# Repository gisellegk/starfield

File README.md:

# Starfield
May the force be with you

Arduino Libraries:
- [kriswiner/LP5036](https://github.com/kriswiner/LP5036/tree/master)
- [JackDaviesDesign/Pimoroni-11x7-LED-Matrix-Arduino](https://github.com/JackDaviesDesign/Pimoroni-11x7-LED-Matrix-Arduino)

Font:
- [Star Jedi](https://www.dafont.com/star-jedi.font)

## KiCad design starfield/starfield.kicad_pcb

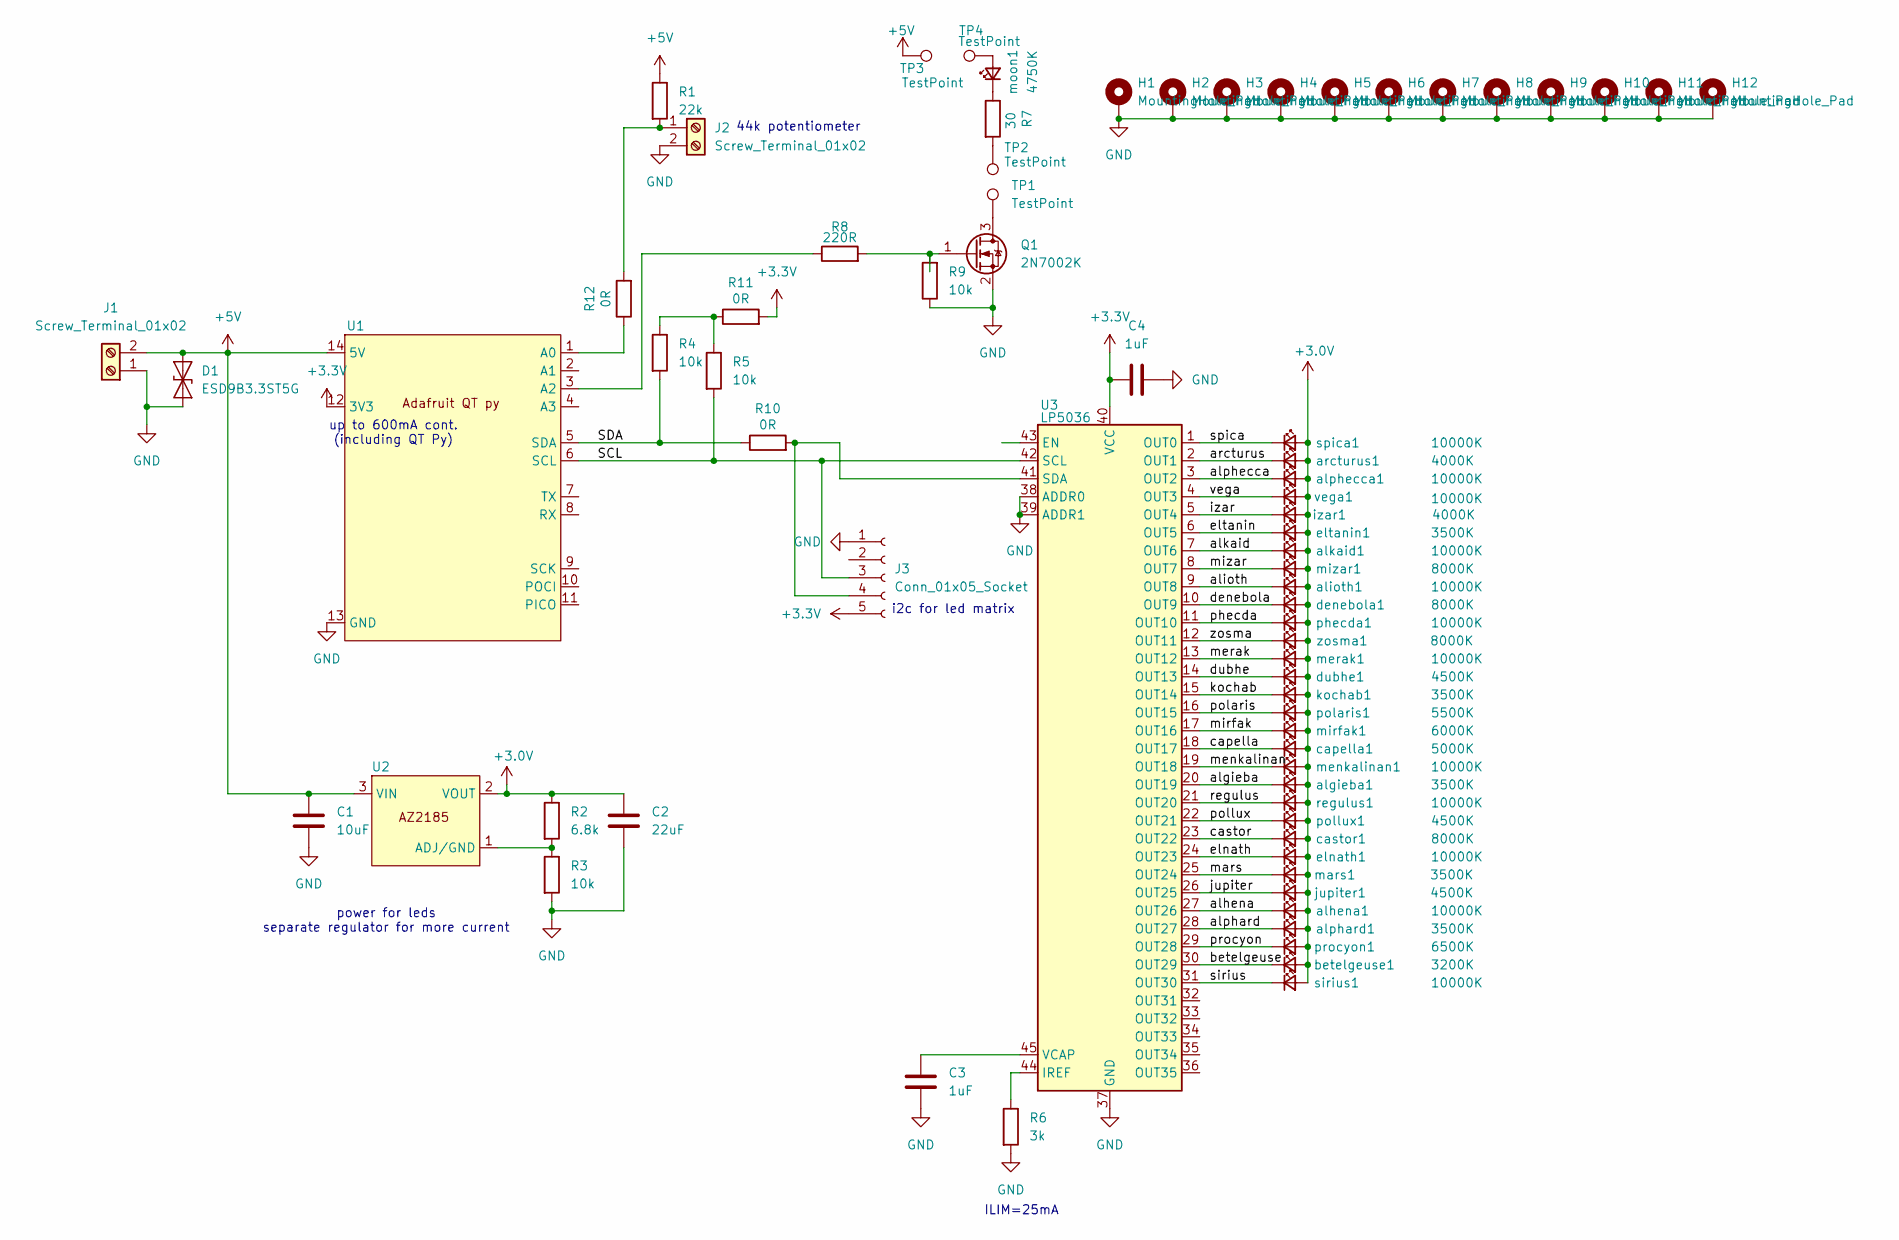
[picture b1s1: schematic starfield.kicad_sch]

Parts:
C1: 10uF; C_0402_1005Metric
C2: 22uF; C_0402_1005Metric
C3, C4: 1uF; C_0402_1005Metric
D1: ESD9B3.3ST5G; D_SOD-923
H1, H2, H3, H4, H5, H6, H7, H8, H9, H10, H11, H12: MountingHole_Pad; MountingHole_3.2mm_M3
J1, J2: Screw_Terminal_01x02; TBLH11-350-02BK
J3: Conn_01x05_Socket; M207910542R
Q1: 2N7002K; SOT-23
R1: 22k; R_0402_1005Metric
R2: 6.8k; R_0402_1005Metric
R3, R4, R5, R9: 10k; R_0402_1005Metric
R6: 3k; R_0402_1005Metric
R7: 30; R_0805_2012Metric
R8: 220R; R_0402_1005Metric
R10, R11, R12: 0R; R_1206_3216Metric
TP1, TP2, TP3, TP4: TestPoint; TestPoint_Keystone_5015_Micro_Mini
U1: XIAO-SAMD21-SMD
U2: AZ2185
U3: LP5036; VQFN-46-1EP_5x6mm_P0.4mm_EP2.8x3.8mm
algieba1: 3500K; ASMY-CWG0-Nxxx2-revmnt
alhena1: 10000K; LUXEON-3014-revmnt
alioth1: 10000K; LUXEON-3014-revmnt
alkaid1: 10000K; LUXEON-3014-revmnt
alphard1: 3500K; ASMY-CWG0-Nxxx2-revmnt
alphecca1: 10000K; LUXEON-3014-revmnt
arcturus1: 4000K; ASMY-CWG0-Nxxx2-revmnt
betelgeuse1: 3200K; ASMY-CWG0-Nxxx2-revmnt
capella1: 5000K; ASMY-CWG0-Nxxx2-revmnt
castor1: 8000K; ASMY-CWG0-Nxxx2-revmnt
denebola1: 8000K; ASMY-CWG0-Nxxx2-revmnt
dubhe1: 4500K; ASMY-CWG0-Nxxx2-revmnt
elnath1: 10000K; LUXEON-3014-revmnt
eltanin1: 3500K; ASMY-CWG0-Nxxx2-revmnt
izar1: 4000K; ASMY-CWG0-Nxxx2-revmnt
jupiter1: 4500K; ASMY-CWG0-Nxxx2-revmnt
kochab1: 3500K; ASMY-CWG0-Nxxx2-revmnt
mars1: 3500K; ASMY-CWG0-Nxxx2-revmnt
menkalinan1: 10000K; LUXEON-3014-revmnt
merak1: 10000K; LUXEON-3014-revmnt
mirfak1: 6000K; WL-SWTP-revmnt
mizar1: 8000K; ASMY-CWG0-Nxxx2-revmnt
moon1: 4750K; moon
phecda1: 10000K; LUXEON-3014-revmnt
polaris1: 5500K; ASMY-CWG0-Nxxx2-revmnt
pollux1: 4500K; ASMY-CWG0-Nxxx2-revmnt
procyon1: 6500K; ASMY-CWG0-Nxxx2-revmnt
regulus1: 10000K; LUXEON-3014-revmnt
sirius1: 10000K; LUXEON-3014-revmnt
spica1: 10000K; LUXEON-3014-revmnt
vega1: 10000K; LUXEON-3014-revmnt
zosma1: 8000K; ASMY-CWG0-Nxxx2-revmnt

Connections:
+3.0V: C2.1, R2.1, U2.2 (VOUT), algieba1.2 (A), alhena1.2 (A), alioth1.2 (A), alkaid1.2 (A), alphard1.2 (A), alphecca1.2 (A), arcturus1.2 (A), betelgeuse1.2 (A), capella1.2 (A), castor1.2 (A), denebola1.2 (A), dubhe1.2 (A), elnath1.2 (A), eltanin1.2 (A), izar1.2 (A), jupiter1.2 (A), kochab1.2 (A), mars1.2 (A), menkalinan1.2 (A), merak1.2 (A), mirfak1.2 (A), mizar1.2 (A), phecda1.2 (A), polaris1.2 (A), pollux1.2 (A), procyon1.2 (A), regulus1.2 (A), sirius1.2 (A), spica1.2 (A), vega1.2 (A), zosma1.2 (A)
+3.3V: C4.1, J3.5, R11.2, U1.12 (3V3), U3.40 (VCC)
+5V: C1.1, D1.1 (A1), J1.2, R1.1, TP3.1, U1.14 (5V), U2.3 (VIN)
/SCL: J3.3, R5.2, U1.6 (SCL), U3.42 (SCL)
/SDA: R4.2, R10.1, U1.5 (SDA)
/algieba: U3.20 (OUT19), algieba1.1 (K)
/alhena: U3.27 (OUT26), alhena1.1 (K)
/alioth: U3.9 (OUT8), alioth1.1 (K)
/alkaid: U3.7 (OUT6), alkaid1.1 (K)
/alphard: U3.28 (OUT27), alphard1.1 (K)
/alphecca: U3.3 (OUT2), alphecca1.1 (K)
/arcturus: U3.2 (OUT1), arcturus1.1 (K)
/betelgeuse: U3.30 (OUT29), betelgeuse1.1 (K)
/capella: U3.18 (OUT17), capella1.1 (K)
/castor: U3.23 (OUT22), castor1.1 (K)
/denebola: U3.10 (OUT9), denebola1.1 (K)
/dubhe: U3.14 (OUT13), dubhe1.1 (K)
/elnath: U3.24 (OUT23), elnath1.1 (K)
/eltanin: U3.6 (OUT5), eltanin1.1 (K)
/izar: U3.5 (OUT4), izar1.1 (K)
/jupiter: U3.26 (OUT25), jupiter1.1 (K)
/kochab: U3.15 (OUT14), kochab1.1 (K)
/mars: U3.25 (OUT24), mars1.1 (K)
/menkalinan: U3.19 (OUT18), menkalinan1.1 (K)
/merak: U3.13 (OUT12), merak1.1 (K)
/mirfak: U3.17 (OUT16), mirfak1.1 (K)
/mizar: U3.8 (OUT7), mizar1.1 (K)
/phecda: U3.11 (OUT10), phecda1.1 (K)
/polaris: U3.16 (OUT15), polaris1.1 (K)
/pollux: U3.22 (OUT21), pollux1.1 (K)
/procyon: U3.29 (OUT28), procyon1.1 (K)
/regulus: U3.21 (OUT20), regulus1.1 (K)
/sirius: U3.31 (OUT30), sirius1.1 (K)
/spica: U3.1 (OUT0), spica1.1 (K)
/vega: U3.4 (OUT3), vega1.1 (K)
/zosma: U3.12 (OUT11), zosma1.1 (K)
GND: C1.2, C2.2, C3.2, C4.2, D1.2 (A2), H1.1, H2.1, H3.1, H4.1, H5.1, H6.1, H7.1, H8.1, H9.1, H10.1, H11.1, H12.1, J1.1, J2.2, J3.1, Q1.2 (S), R3.2, R6.2, R9.1, U1.13 (GND), U3.37 (GND), U3.38 (ADDR0), U3.39 (ADDR1), U3.46 (GND), U3.47 (GND)
unnamed: J2.1, R1.2, R12.2
unnamed: J3.4, R10.2, U3.41 (SDA)
unnamed: Q1.3 (D), TP1.1
unnamed: Q1.1 (G), R8.2, R9.2
unnamed: R7.2, TP2.1
unnamed: R4.1, R5.1, R11.1
unnamed: R12.1, U1.1 (A0)
unnamed: R8.1, U1.3 (A2)
unnamed: R2.2, R3.1, U2.1 (ADJ/GND)
unnamed: R6.1, U3.44 (IREF)
unnamed: C3.1, U3.45 (VCAP)
unnamed: TP4.1, moon1.2 (A)
unnamed: R7.1, moon1.1 (K)

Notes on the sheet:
power for leds separate regulator for more current
up to 600mA cont. (including QT Py)
i2c for led matrix
ILIM=25mA
44k potentiometer

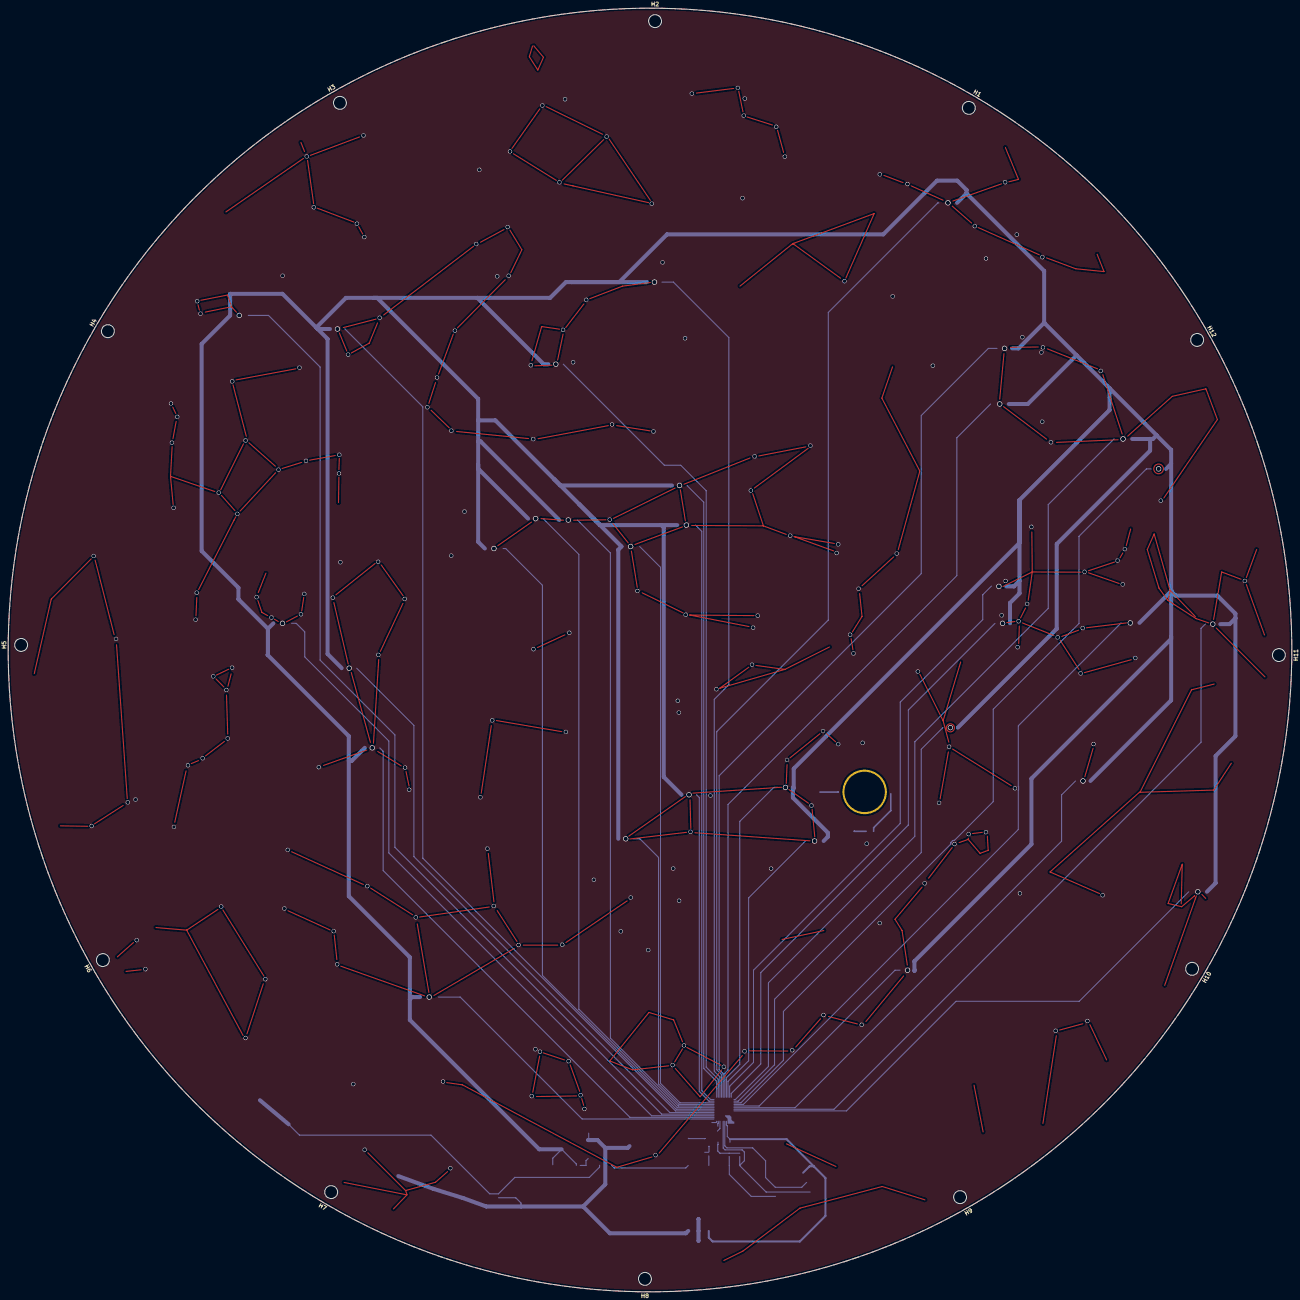
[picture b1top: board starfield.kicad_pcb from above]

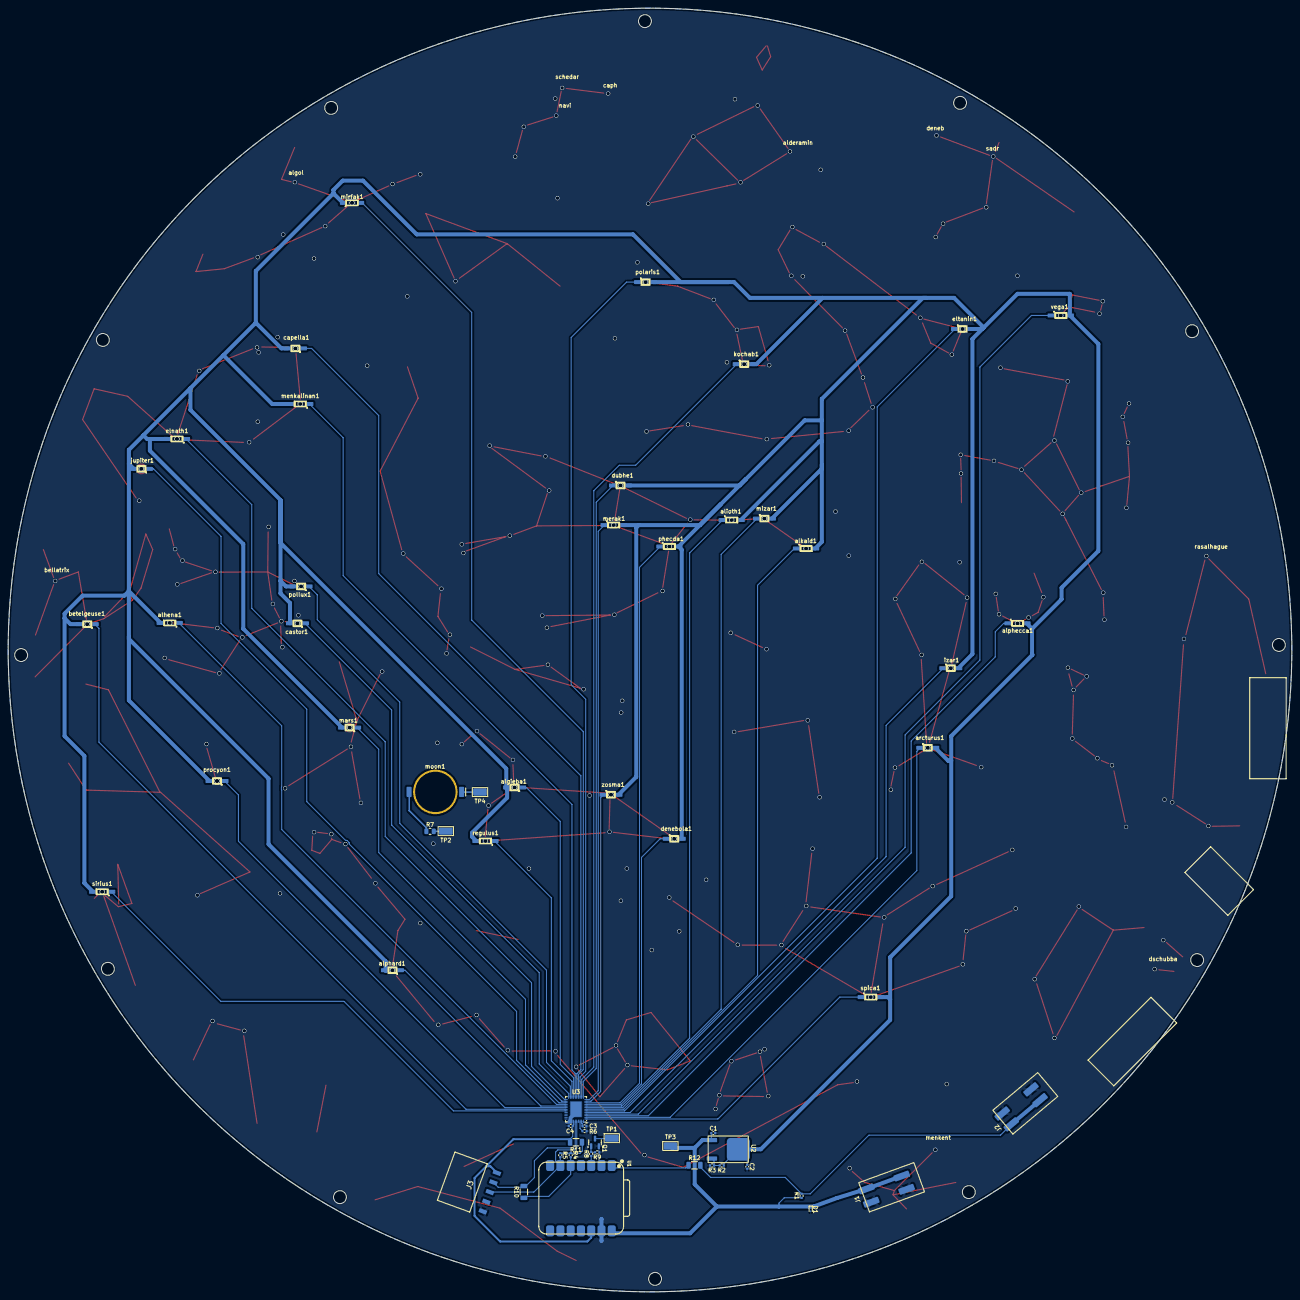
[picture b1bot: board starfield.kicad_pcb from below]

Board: 2 copper layers, 317.5 x 317.5 mm, 74 parts (60 on the bottom side), 50 nets.

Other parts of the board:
brights: LOGO
dims: LOGO

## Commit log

2026-04-27 3d files
2026-04-27 kicad files
2026-04-27 screenshots
2026-05-01 update 3d files
2026-05-03 initial code commit
2026-05-03 Add final frame cad
2026-05-03 Fix bedleveling code to not probe all the way back
2026-05-03 code
2026-05-06 bright stars
2026-05-07 Add final cad
2026-05-24 rewire sirius to ch35
2026-05-26 Add frame
